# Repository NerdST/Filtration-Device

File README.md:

# Filtration-Device
 IED main project.  Will contain webapp and microcontroller software

Gamerville gaming

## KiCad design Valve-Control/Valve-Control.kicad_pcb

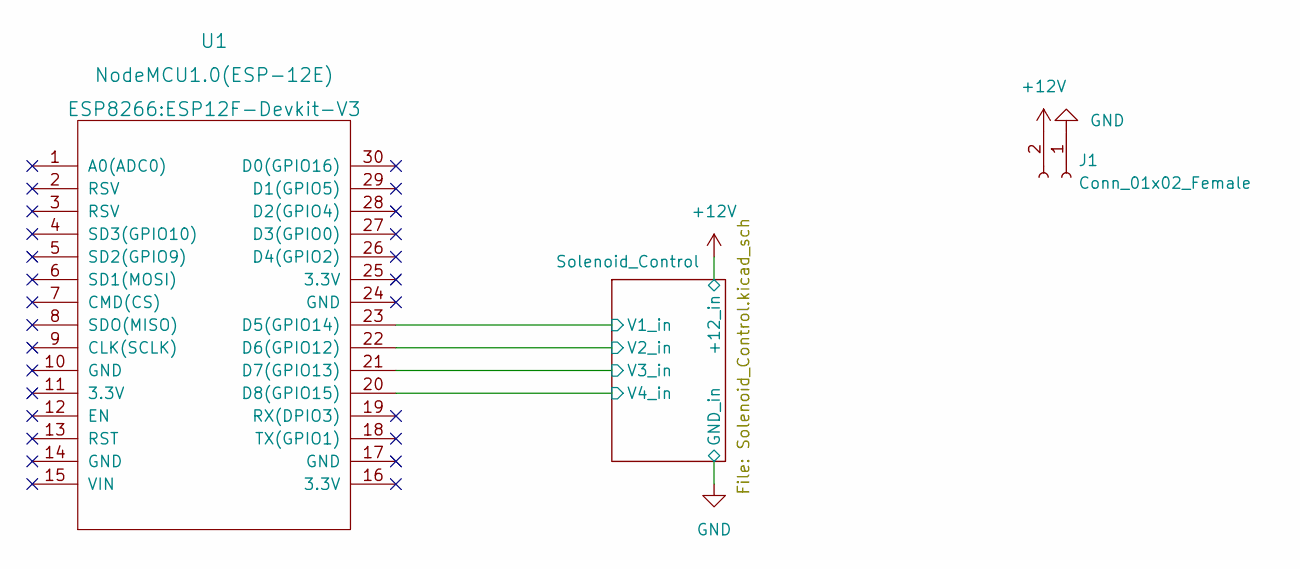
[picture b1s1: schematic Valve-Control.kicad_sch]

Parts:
J1: Conn_01x02_Female; PinHeader_1x02_P1.00mm_Vertical
U1: NodeMCU1.0(ESP-12E); ESP12F-Devkit-V3

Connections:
+12V: J1.2; also elsewhere on the board
/Solenoid_Control/V1_in: U1.23 (D5(GPIO14)); also elsewhere on the board
/Solenoid_Control/V2_in: U1.22 (D6(GPIO12)); also elsewhere on the board
/Solenoid_Control/V3_in: U1.21 (D7(GPIO13)); also elsewhere on the board
/Solenoid_Control/V4_in: U1.20 (D8(GPIO15)); also elsewhere on the board
GND: J1.1; also elsewhere on the board

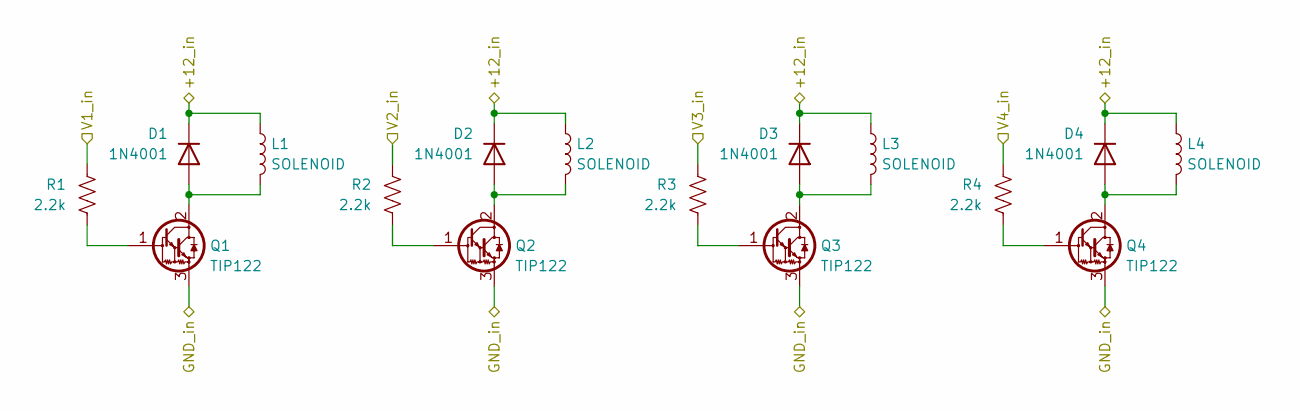
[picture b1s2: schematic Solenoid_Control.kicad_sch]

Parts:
D1, D2, D3, D4: 1N4001; D_DO-41_SOD81_P10.16mm_Horizontal
L1, L2, L3, L4: SOLENOID; PinHeader_1x02_P1.00mm_Vertical
Q1, Q2, Q3, Q4: TIP122; TO-220-3_Vertical
R1, R2, R3, R4: 2.2k; R_Axial_DIN0204_L3.6mm_D1.6mm_P5.08mm_Horizontal

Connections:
+12V: D1.1 (K), D2.1 (K), D3.1 (K), D4.1 (K), L1.1, L2.1, L3.1, L4.1; also elsewhere on the board
/Solenoid_Control/V1_in: R1.1; also elsewhere on the board
/Solenoid_Control/V2_in: R2.1; also elsewhere on the board
/Solenoid_Control/V3_in: R3.1; also elsewhere on the board
/Solenoid_Control/V4_in: R4.1; also elsewhere on the board
GND: Q1.3 (E), Q2.3 (E), Q3.3 (E), Q4.3 (E); also elsewhere on the board
unnamed: D1.2 (A), L1.2, Q1.2 (C)
unnamed: D2.2 (A), L2.2, Q2.2 (C)
unnamed: D3.2 (A), L3.2, Q3.2 (C)
unnamed: D4.2 (A), L4.2, Q4.2 (C)
unnamed: Q1.1 (B), R1.2
unnamed: Q2.1 (B), R2.2
unnamed: Q3.1 (B), R3.2
unnamed: Q4.1 (B), R4.2

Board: 2 copper layers, 18 parts (0 on the bottom side), 14 nets, no tracks yet.

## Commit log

2024-03-12 Created App
2024-03-18 ESP Boilerplate
2024-04-05 A lot of stuff happened
